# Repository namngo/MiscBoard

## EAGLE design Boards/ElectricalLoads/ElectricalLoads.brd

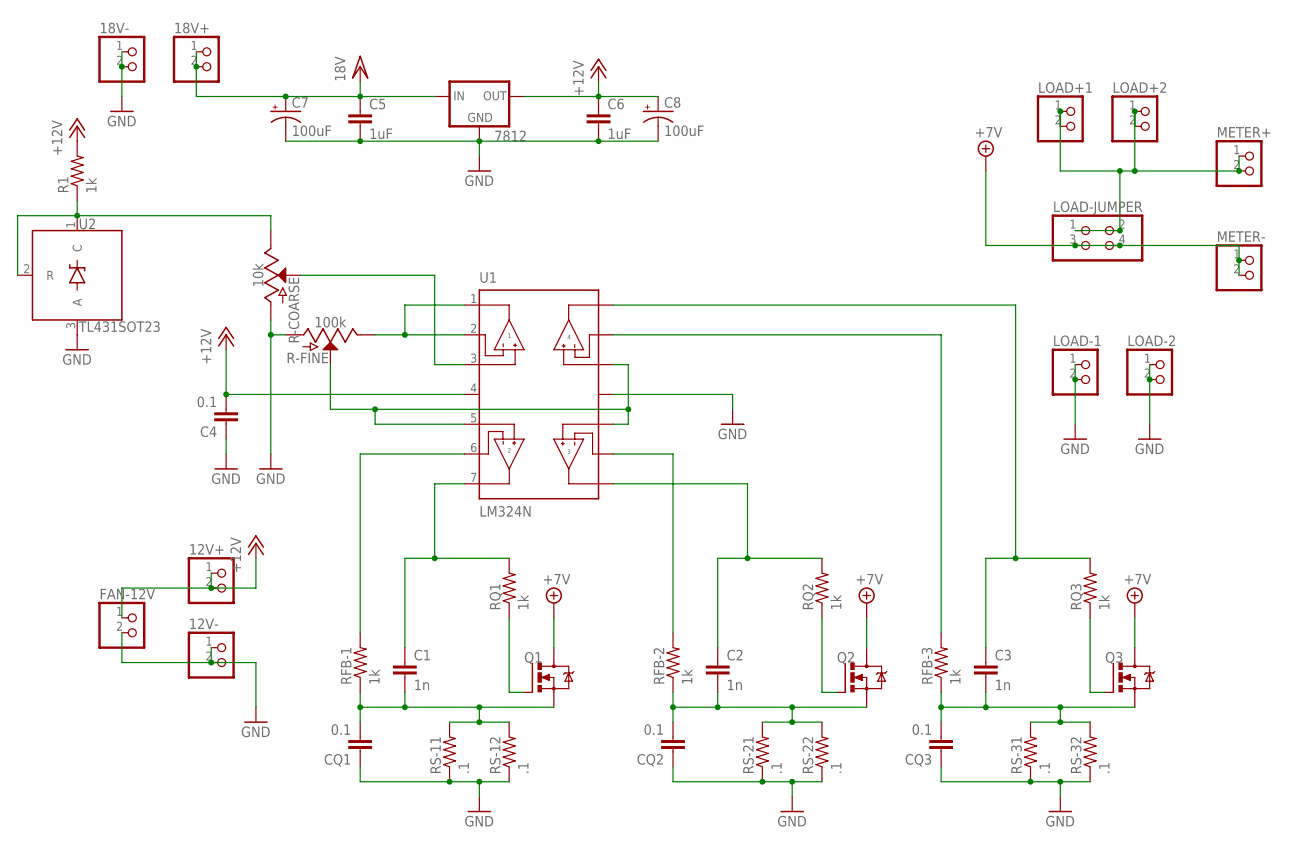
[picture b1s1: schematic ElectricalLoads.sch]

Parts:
12V+, 12V-, 18V+, 18V-: PINHD-1X2; 1X02
7812: V_REG_78XX-TO-220; TO-220-ALT
C1, C2, C3: 1n; 0805
C4: 0.1; 0805
C5, C6: 1uF; 1210
C7, C8: 100uF; PANASONIC_D
CQ1, CQ2, CQ3: 0.1; 0805
FAN-12V: PINHD-1X2; 1X02
LOAD+1, LOAD+2: PINHD-1X2; 1X02
LOAD-1, LOAD-2: PINHD-1X2; 1X02
LOAD-JUMPER: PINHD-2X2; 2X02
METER+: PINHD-1X2; 1X02
METER-: PINHD-1X2; 1X02
Q1, Q2, Q3: IRLZ44Z; TO220BH
R1: 1k; M0805
R-COARSE: 10k; POT-PTH-ALPS
R-FINE: 100k; POT-PTH-ALPS
RFB-1, RFB-2, RFB-3: 1k; M0805
RQ1, RQ2, RQ3: 1k; M0805
RS-11, RS-12, RS-21, RS-22, RS-31, RS-32: .1; M1206
U1: LM324N; DIP762W45P254L1969H508Q14
U2: TL431SOT23; SOT23-3

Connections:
+7V: LOAD-JUMPER.3, LOAD-JUMPER.4, METER-.1, METER-.2, Q1.D, Q2.D, Q3.D
+12V: 12V+.1, 12V+.2, 7812.OUT, C4.2, C6.1, C8.+, FAN-12V.1, R1.2, U1.4 (VCC)
GND: 12V-.1, 12V-.2, 18V-.1, 18V-.2, 7812.GND, C4.1, C5.2, C6.2, C7.-, C8.-, CQ1.1, CQ2.1, CQ3.1, FAN-12V.2, LOAD-1.1, LOAD-1.2, LOAD-2.1, LOAD-2.2, R-COARSE.P$3 (A), R-FINE.P$3 (A), RS-11.1, RS-12.1, RS-21.1, RS-22.1, RS-31.1, RS-32.1, U1.11 (GND), U2.3 (A); also elsewhere on the board
unnamed: C1.2, CQ1.2, Q1.S, RFB-1.1, RS-11.2, RS-12.2
unnamed: Q1.G, RQ1.1
unnamed: C1.1, RQ1.2, U1.7 (2OUT)
unnamed: RFB-1.2, U1.6 (2IN-)
unnamed: C2.2, CQ2.2, Q2.S, RFB-2.1, RS-21.2, RS-22.2
unnamed: Q2.G, RQ2.1
unnamed: C2.1, RQ2.2, U1.8 (3OUT)
unnamed: RFB-2.2, U1.9 (3IN-)
unnamed: C3.2, CQ3.2, Q3.S, RFB-3.1, RS-31.2, RS-32.2
unnamed: Q3.G, RQ3.1
unnamed: R1.1, R-COARSE.P$1 (E), U2.1 (C), U2.2 (R)
unnamed: C3.1, RQ3.2, U1.14 (4OUT)
unnamed: RFB-3.2, U1.13 (4IN-)
unnamed: R-COARSE.P$2 (S), U1.3 (1IN+)
unnamed: R-FINE.P$2 (S), U1.5 (2IN+), U1.10 (3IN+), U1.12 (4IN+)
unnamed: R-FINE.P$1 (E), U1.1 (1OUT), U1.2 (1IN-)
unnamed: LOAD+1.1, LOAD+1.2, LOAD+2.1, LOAD+2.2, LOAD-JUMPER.1, LOAD-JUMPER.2, METER+.1, METER+.2
VCC/2: 18V+.1, 18V+.2, 7812.IN, C5.1, C7.+

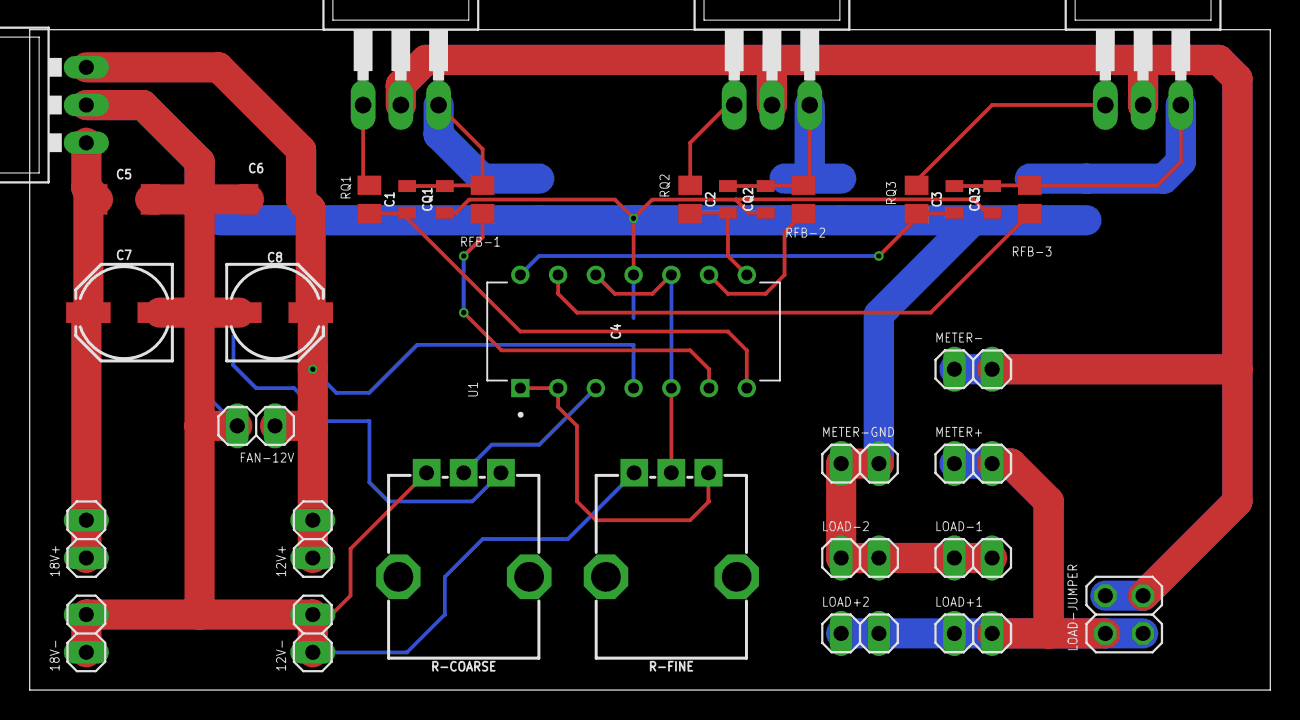
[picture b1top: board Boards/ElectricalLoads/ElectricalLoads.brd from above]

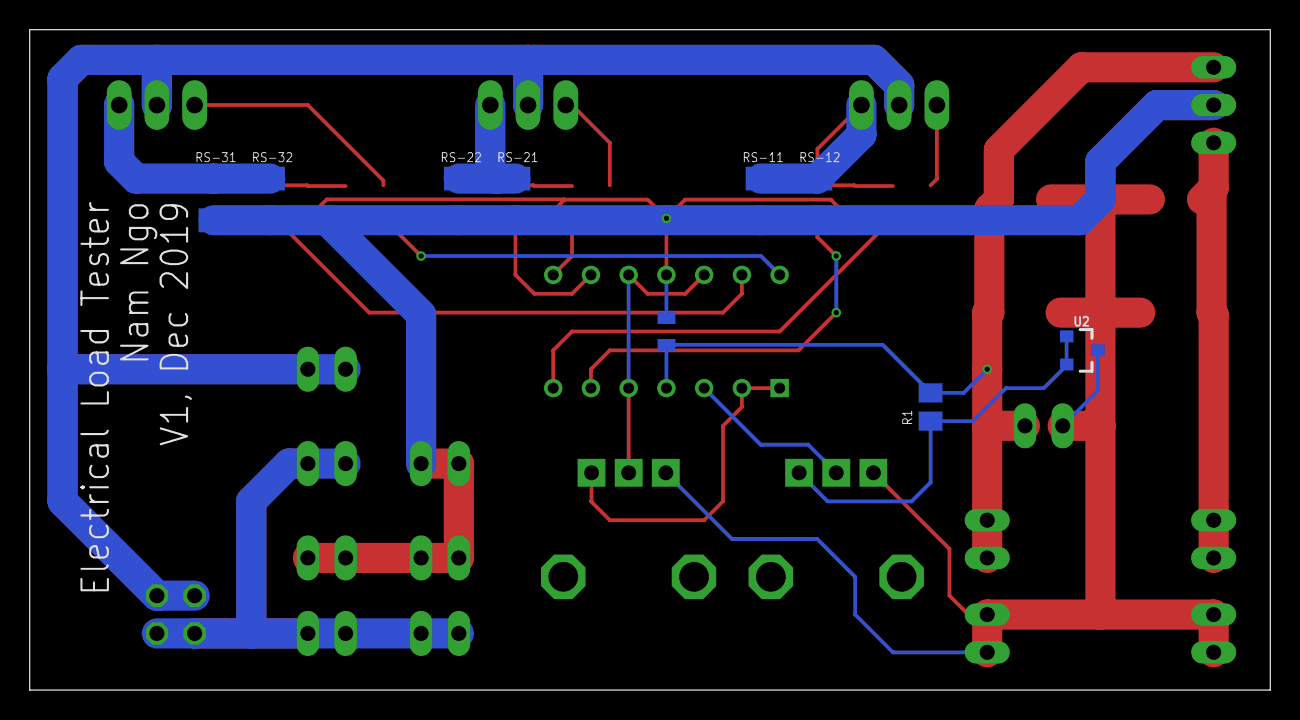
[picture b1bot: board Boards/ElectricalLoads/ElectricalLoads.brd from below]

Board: 2 copper layers, 83.5 x 44.4 mm, 45 parts (9 on the bottom side), 21 nets.

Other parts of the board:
METER-GND: 1X02

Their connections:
GND: METER-GND.1, METER-GND.2; also elsewhere on the board

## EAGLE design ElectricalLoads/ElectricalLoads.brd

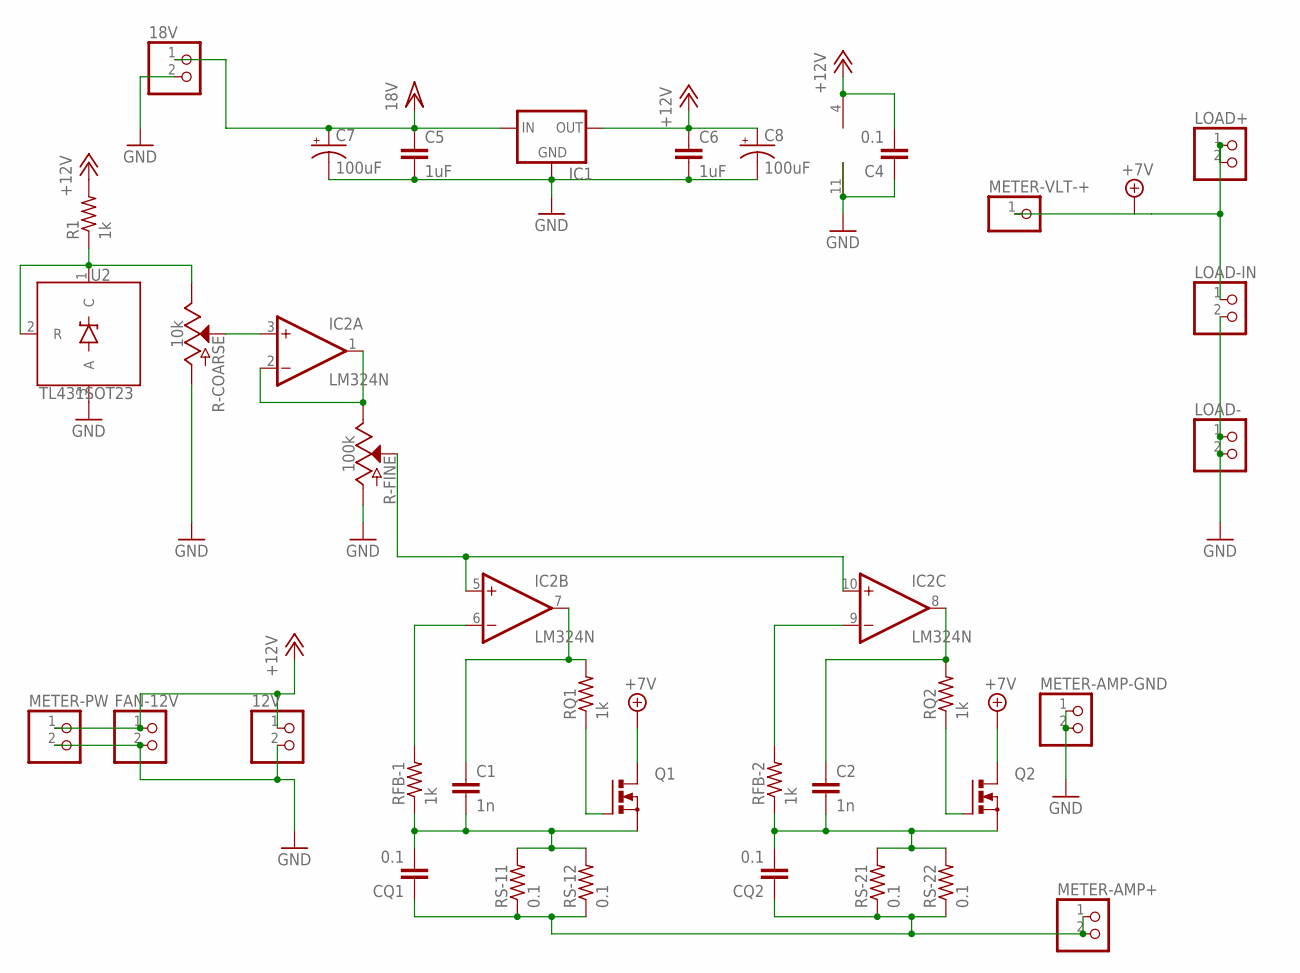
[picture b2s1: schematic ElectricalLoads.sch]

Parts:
12V, 18V: PINHD-1X2; 1X02
C1, C2: 1n; 0805
C4: 0.1; 0805
C5, C6: 1uF; 1210
C7, C8: 100uF; PANASONIC_D
CQ1, CQ2: 0.1; 0805
FAN-12V: PINHD-1X2; 1X02
IC1: 78XXS
IC2: LM324N; DIL14
LOAD+: PINHD-1X2; 1X02
LOAD-: PINHD-1X2; 1X02
LOAD-IN: PINHD-1X2; 1X02
METER-AMP+: PINHD-1X2; 1X02
METER-AMP-GND: PINHD-1X2; 1X02
METER-PW: PINHD-1X2; 1X02
METER-VLT-+: PINHD-1X1; 1X01
Q1, Q2: PMOSFET_NTO220BH; TO220BH
R1: 1k; M0805
R-COARSE: 10k; POT-PTH-ALPS
R-FINE: 100k; POT-PTH-ALPS
RFB-1, RFB-2: 1k; M0805
RQ1, RQ2: 1k; M0805
RS-11, RS-12, RS-21, RS-22: 0.1; R2512
U2: TL431SOT23; SOT23-3

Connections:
+7V: LOAD+.1, LOAD+.2, LOAD-IN.1, METER-VLT-+.1, Q1.D, Q2.D
+12V: 12V.1, C4.2, C6.1, C8.+, FAN-12V.1, IC1.OUT, IC2.4 (V+), METER-PW.1, R1.2
GND: 12V.2, 18V.2, C4.1, C5.2, C6.2, C7.-, C8.-, FAN-12V.2, IC1.GND, IC2.11 (V-), LOAD-.1, LOAD-.2, LOAD-IN.2, METER-AMP-GND.1, METER-AMP-GND.2, METER-PW.2, R-COARSE.P$3 (A), R-FINE.P$3 (A), U2.3 (A)
unnamed: C1.2, CQ1.2, Q1.S, RFB-1.1, RS-11.2, RS-12.2
unnamed: Q1.G, RQ1.1
unnamed: IC2.3 (+IN), R-COARSE.P$2 (S)
unnamed: C1.1, IC2.7 (OUT), RQ1.2
unnamed: IC2.6 (-IN), RFB-1.2
unnamed: C2.2, CQ2.2, Q2.S, RFB-2.1, RS-21.2, RS-22.2
unnamed: Q2.G, RQ2.1
unnamed: C2.1, IC2.8 (OUT), RQ2.2
unnamed: IC2.9 (-IN), RFB-2.2
unnamed: R1.1, R-COARSE.P$1 (E), U2.1 (C), U2.2 (R)
unnamed: CQ1.1, CQ2.1, METER-AMP+.1, METER-AMP+.2, RS-11.1, RS-12.1, RS-21.1, RS-22.1
unnamed: IC2.5 (+IN), IC2.10 (+IN), R-FINE.P$2 (S)
unnamed: IC2.1 (OUT), IC2.2 (-IN), R-FINE.P$1 (E)
VCC/2: 18V.1, C5.1, C7.+, IC1.IN

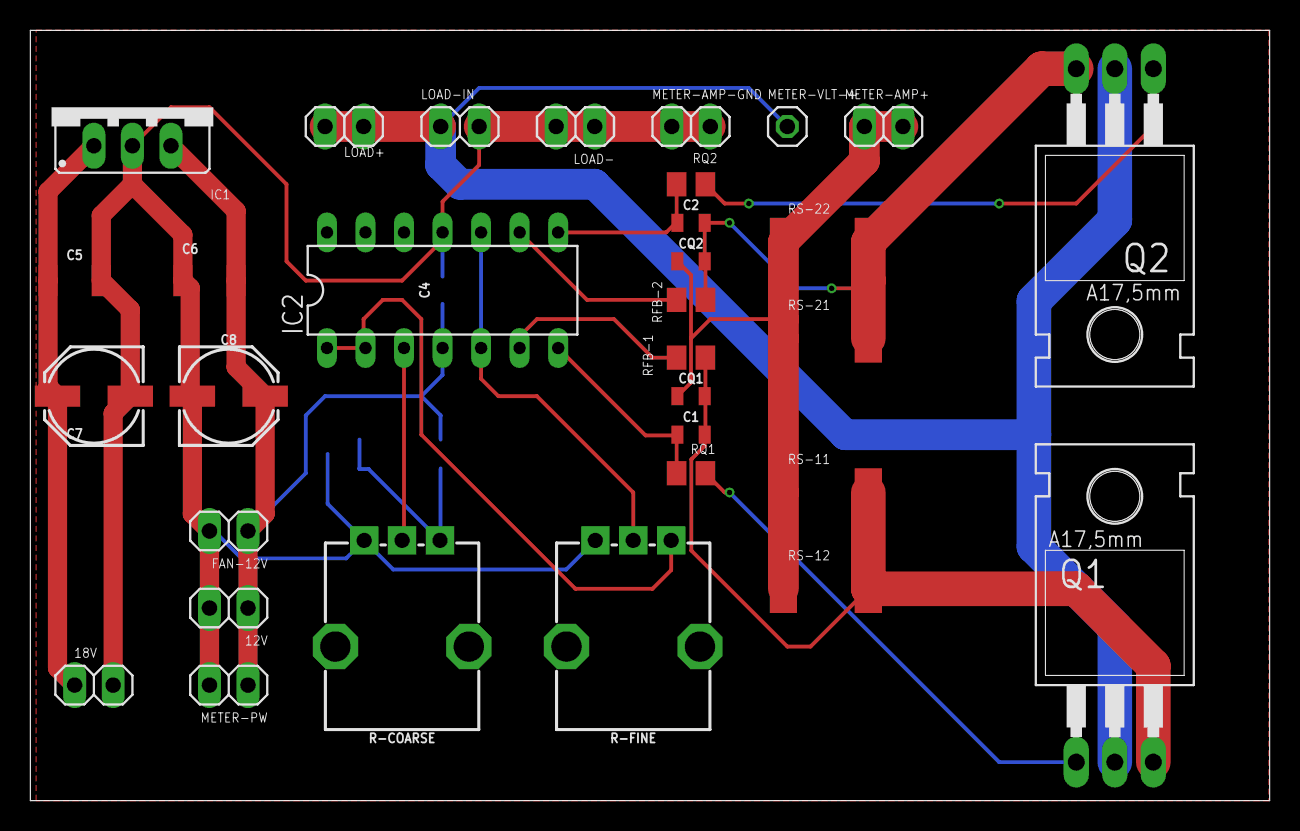
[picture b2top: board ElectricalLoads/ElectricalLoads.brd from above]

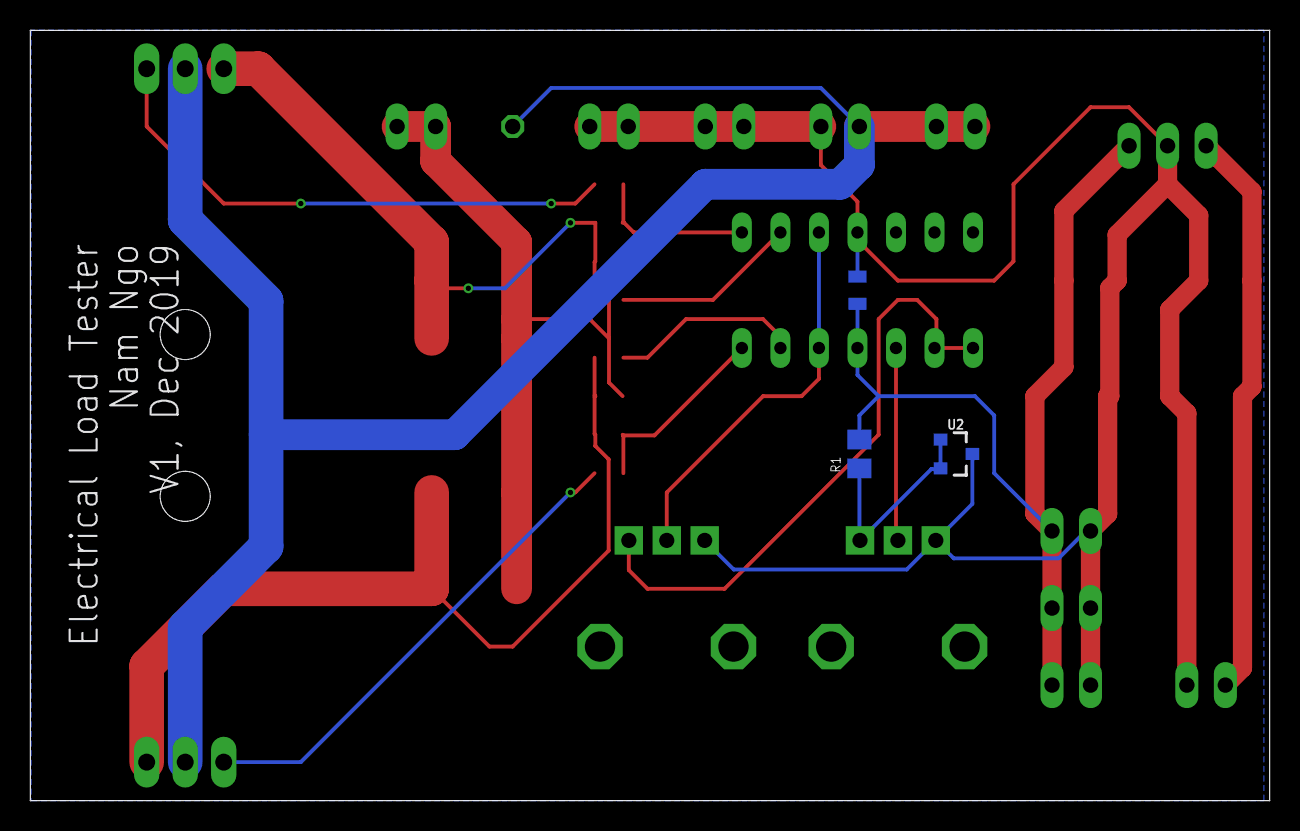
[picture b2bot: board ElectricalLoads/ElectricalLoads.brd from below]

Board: 2 copper layers, 81.7 x 50.8 mm, 35 parts (3 on the bottom side), 17 nets.

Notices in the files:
parts and their libraries:
SparkFun-IC-Power: Licensing: Creative Commons ShareAlike 4.0 International - https://creativecommons.org/licenses/by-sa/4.0
